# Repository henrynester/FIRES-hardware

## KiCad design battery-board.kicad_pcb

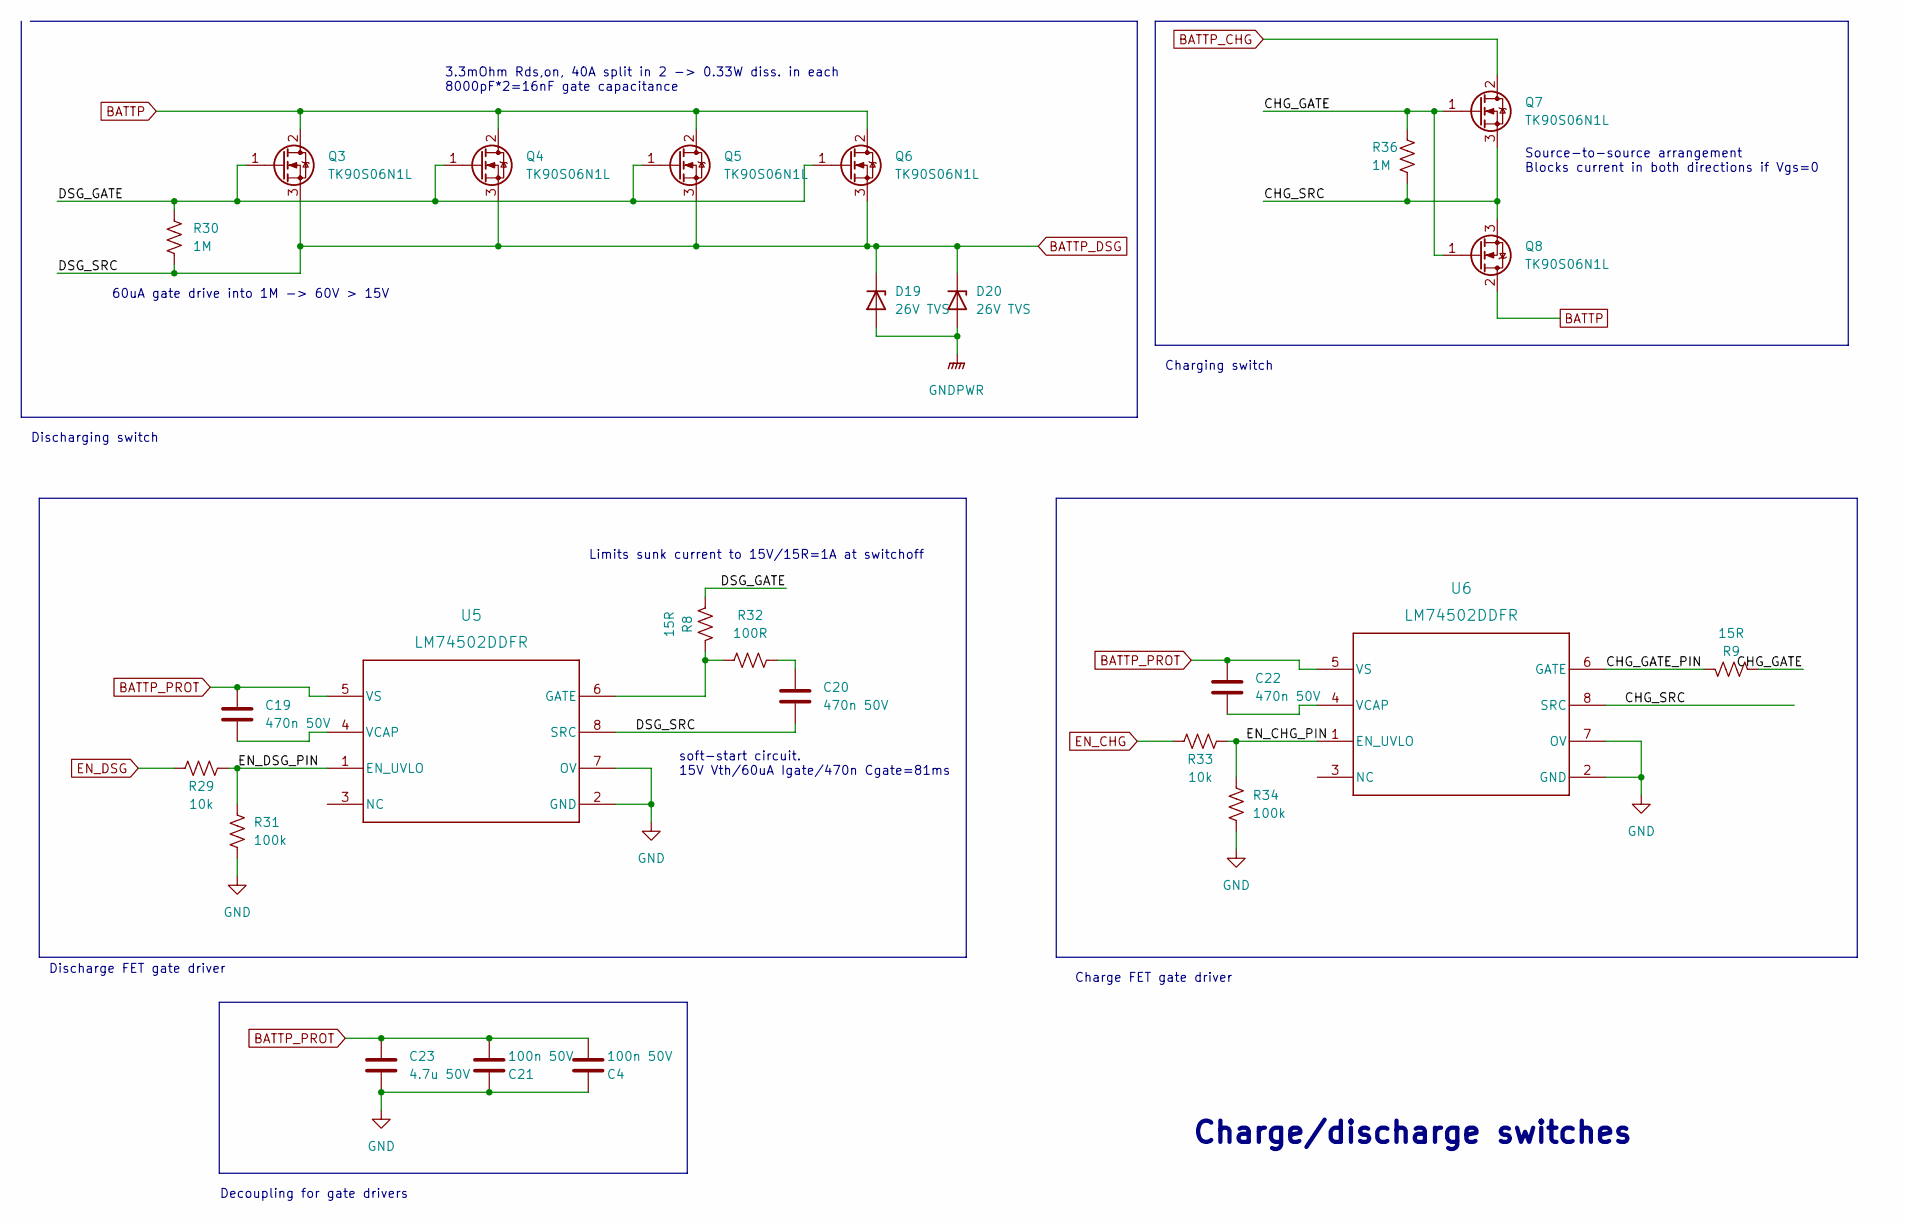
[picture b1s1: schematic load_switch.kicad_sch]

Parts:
C4, C21: 100n 50V; C_0805_2012Metric; part_number GCD21BR71H104KA01L
C19, C20, C22: 470n 50V; C_0805_2012Metric_Pad1.18x1.45mm_HandSolder; part_number GRM21BR71H474KA88L
C23: 4.7u 50V; C_1206_3216Metric_Pad1.33x1.80mm_HandSolder; part_number GRM31CR71H475KA12L
D19, D20: 26V TVS; D_SMB; part_number SMBJ26A
Q3, Q4, Q5, Q6, Q7, Q8: TK90S06N1L; TO-252-2; part_number TK90S06N1L,LXHQ
R8, R9: 15R; R_0805_2012Metric_Pad1.20x1.40mm_HandSolder; part_number RC0805FR-1310KL
R29, R33: 10k; R_0805_2012Metric_Pad1.20x1.40mm_HandSolder; part_number RC0805FR-1310KL
R30, R36: 1M; R_0805_2012Metric_Pad1.20x1.40mm_HandSolder; part_number RC0805FR-071ML
R31, R34: 100k; R_0805_2012Metric_Pad1.20x1.40mm_HandSolder; part_number RC0805FR-07100KL
R32: 100R; R_0805_2012Metric_Pad1.20x1.40mm_HandSolder; part_number RC0805FR-07100RL
U5, U6: LM74502DDFR; LM74502; part_number LM74502DDFR

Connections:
/load_switch/CHG_GATE: Q7.1 (G), Q8.1 (G), R9.2, R36.1
/load_switch/CHG_GATE_PIN: R9.1, U6.6 (GATE)
/load_switch/CHG_SRC: Q7.3 (S), Q8.3 (S), R36.2, U6.8 (SRC)
/load_switch/DSG_GATE: Q3.1 (G), Q4.1 (G), Q5.1 (G), Q6.1 (G), R8.2, R30.1
/load_switch/EN_CHG_PIN: R33.2, R34.1, U6.1 (EN_UVLO)
/load_switch/EN_DSG_PIN: R29.2, R31.1, U5.1 (EN_UVLO)
BATTN: C4.1, C21.1, C23.2, R31.2, R34.2, U5.2 (GND), U5.7 (OV), U6.2 (GND), U6.7 (OV); also elsewhere on the board
BATTP: Q3.2 (D), Q4.2 (D), Q5.2 (D), Q6.2 (D), Q8.2 (D); also elsewhere on the board
BATTP_CHG: Q7.2 (D); also elsewhere on the board
BATTP_DSG: C20.2, D19.1 (K), D20.1 (K), Q3.3 (S), Q4.3 (S), Q5.3 (S), Q6.3 (S), R30.2, U5.8 (SRC); also elsewhere on the board
BATTP_PROT: C4.2, C19.1, C21.2, C22.1, C23.1, U5.5 (VS), U6.5 (VS); also elsewhere on the board
EN_CHG: R33.1; also elsewhere on the board
EN_DSG: R29.1; also elsewhere on the board
GNDPWR: D19.2 (A), D20.2 (A); also elsewhere on the board
unnamed: C19.2, U5.4 (VCAP)
unnamed: C20.1, R32.2
unnamed: C22.2, U6.4 (VCAP)
unnamed: R8.1, R32.1, U5.6 (GATE)

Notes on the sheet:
Charge FET gate driver
Decoupling for gate drivers
soft-start circuit. 15V Vth/60uA Igate/470n Cgate=81ms
Charging switch
Charge/discharge switches
Discharging switch
Discharge FET gate driver
Source-to-source arrangement Blocks current in both directions if Vgs=0
Limits sunk current to 15V/15R=1A at switchoff
60uA gate drive into 1M -> 60V > 15V
3.3mOhm Rds,on, 40A split in 2 -> 0.33W diss. in each 8000pF*2=16nF gate capacitance

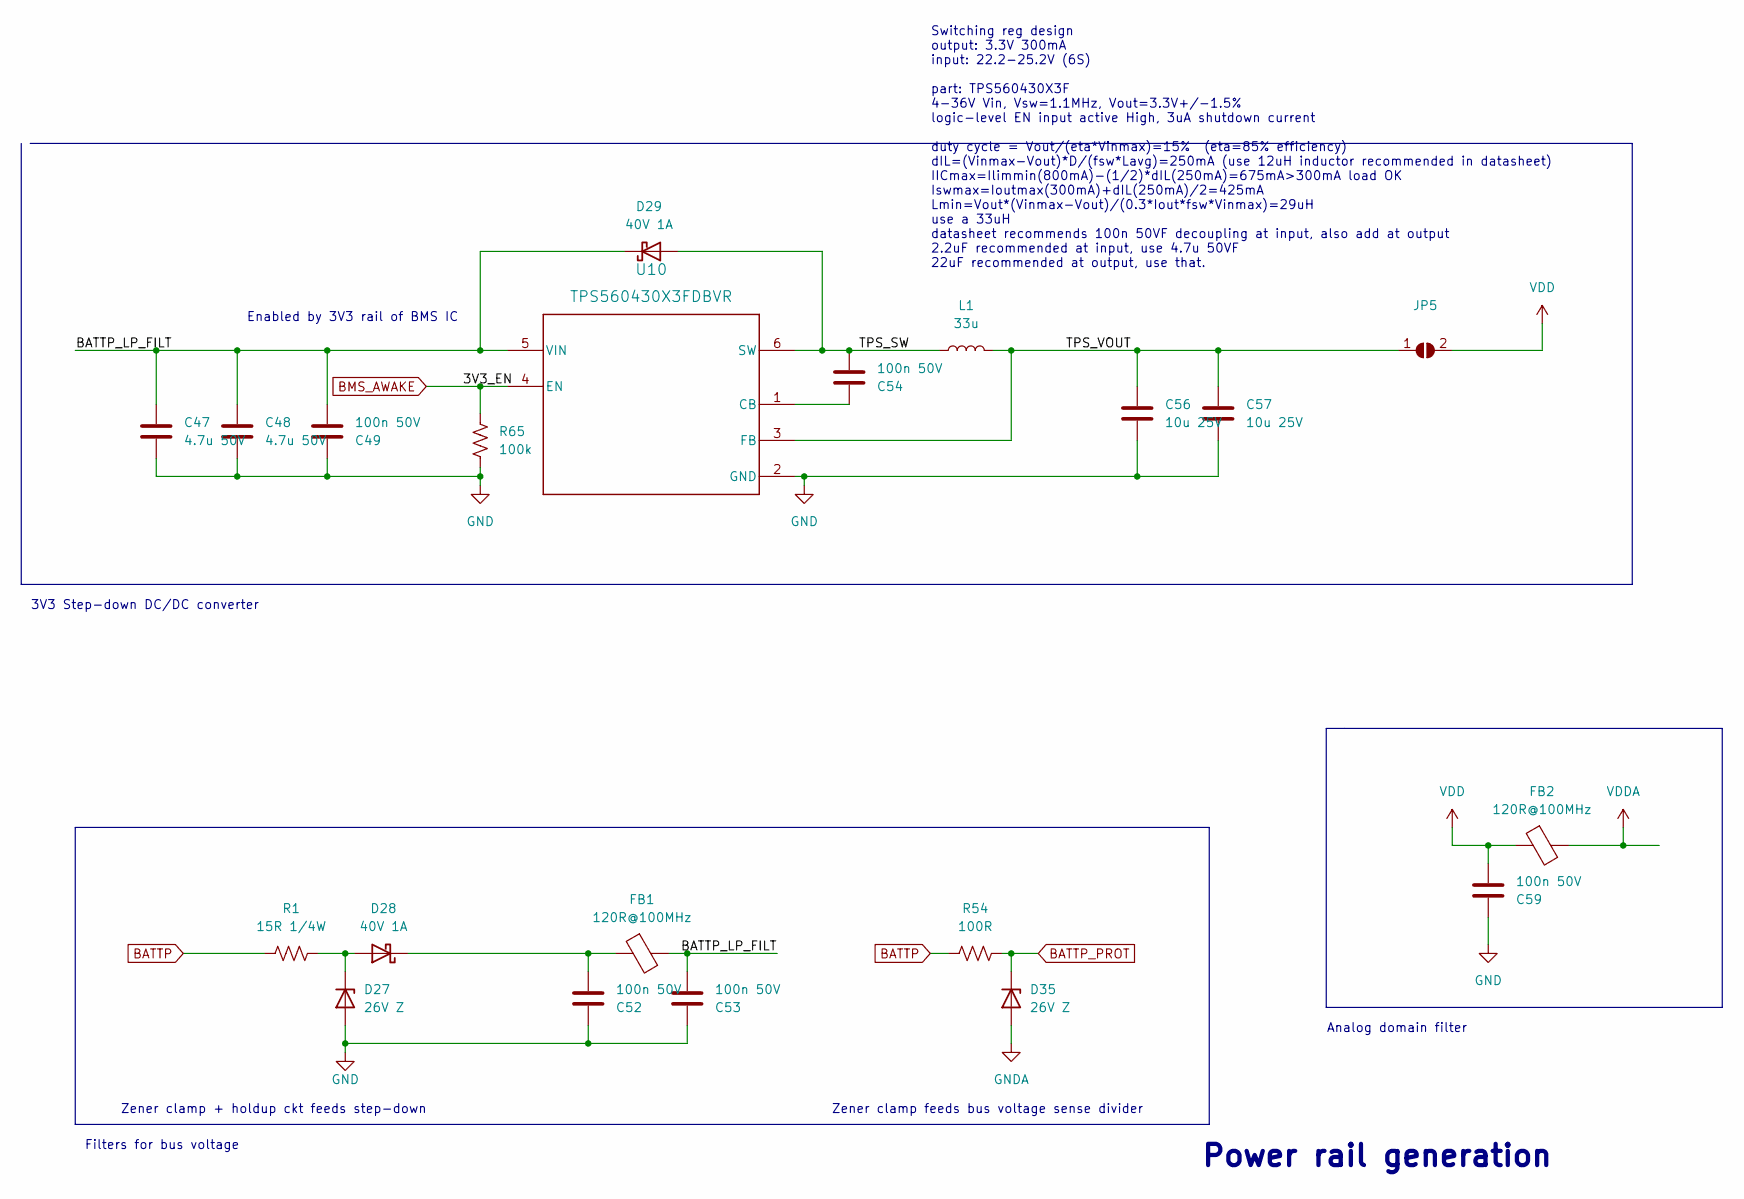
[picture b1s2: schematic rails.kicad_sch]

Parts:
C47, C48: 4.7u 50V; C_1206_3216Metric_Pad1.33x1.80mm_HandSolder; part_number GRM31CR71H475KA12L
C49, C52, C53, C54, C59: 100n 50V; C_0805_2012Metric; part_number GCD21BR71H104KA01L
C56, C57: 10u 25V; C_1206_3216Metric_Pad1.33x1.80mm_HandSolder; part_number GRM31CR71E106KA12L
D27, D35: 26V Z; D_SOD-123; part_number DDZ26-7
D28, D29: 40V 1A; D_SOD-323_HandSoldering; part_number 1N5819WS
FB1, FB2: 120R@100MHz; R_0805_2012Metric; part_number HI0805O121R-10
JP5: SolderJumper-2_P1.3mm_Open_Pad1.0x1.5mm
L1: 33u; L_Taiyo-Yuden_NR-60xx; part_number NR6028T330M
R1: 15R 1/4W; R_0805_2012Metric_Pad1.20x1.40mm_HandSolder; part_number AC0805FR-7W15RL
R54: 100R; R_0805_2012Metric_Pad1.20x1.40mm_HandSolder; part_number RC0805FR-07100RL
R65: 100k; R_0805_2012Metric_Pad1.20x1.40mm_HandSolder; part_number RC0805FR-07100KL
U10: TPS560430X3FDBVR; SOT-23-6_Handsoldering; part_number TPS560430X3FDBVR

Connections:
/rails/BATTP_LP_FILT: C47.1, C48.1, C49.2, C53.2, D29.1 (K), FB1.2, U10.5 (VIN)
/rails/TPS_SW: C54.2, D29.2 (A), L1.1, U10.6 (SW)
/rails/TPS_VOUT: C56.1, C57.1, JP5.1 (A), L1.2, U10.3 (FB)
BATTN: C47.2, C48.2, C49.1, C52.1, C53.1, C56.2, C57.2, C59.1, D27.2 (A), D35.2 (A), R65.1, U10.2 (GND); also elsewhere on the board
BATTP: R1.1, R54.1; also elsewhere on the board
BATTP_PROT: D35.1 (K), R54.2; also elsewhere on the board
BMS_AWAKE: R65.2, U10.4 (EN); also elsewhere on the board
unnamed: C52.2, D28.1 (K), FB1.1
unnamed: C54.1, U10.1 (CB)
unnamed: D27.1 (K), D28.2 (A), R1.2
VDD: C59.2, FB2.1, JP5.2 (B); also elsewhere on the board
VDDA: FB2.2; also elsewhere on the board

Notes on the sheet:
3V3 Step-down DC/DC converter
Analog domain filter
Zener clamp feeds bus voltage sense divider
Power rail generation
Switching reg design output: 3.3V 300mA input: 22.2-25.2V (6S) part: TPS560430X3F 4-36V Vin, Vsw=1.1MHz, Vout=3.3V+/-1.5% logic-level EN input active High, 3uA shutdown current duty cycle = Vout/(eta*Vinmax)=15% (eta=85% efficiency) dIL=(Vinmax-Vout)*D/(fsw*Lavg)=250mA (use 12uH inductor recommende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
Filters for bus voltage
Zener clamp + holdup ckt feeds step-down
Enabled by 3V3 rail of BMS IC

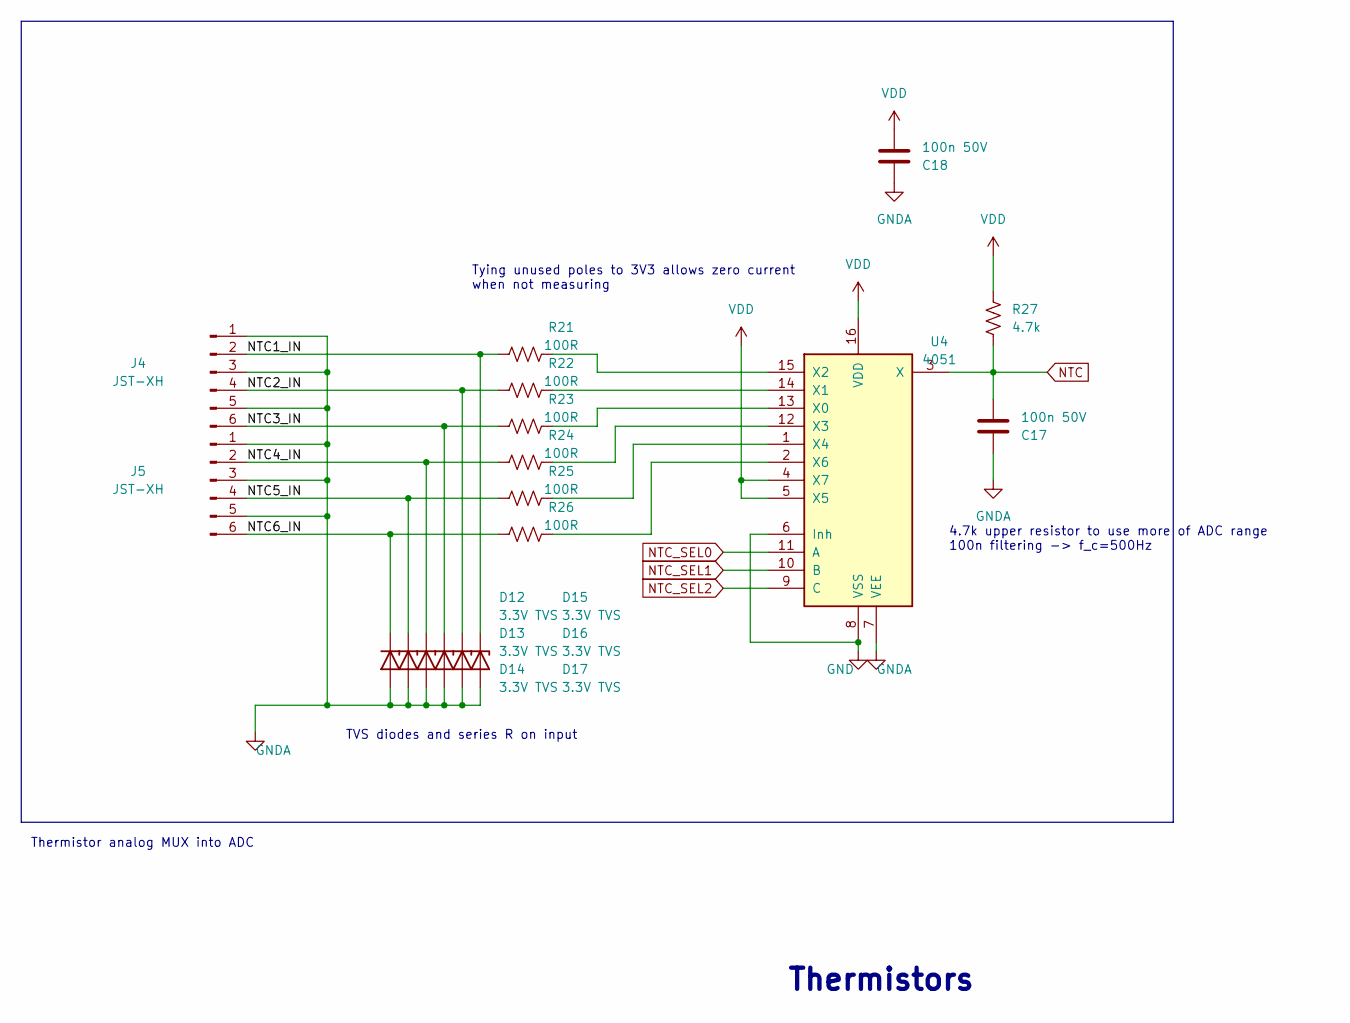
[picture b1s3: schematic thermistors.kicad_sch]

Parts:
C17, C18: 100n 50V; C_0805_2012Metric; part_number GCD21BR71H104KA01L
D12, D13, D14, D15, D16, D17: 3.3V TVS; D_SOD-323_HandSoldering; part_number ESD5Z3.3T5G
J4, J5: JST-XH; JST_XH_B6B-XH-A_1x06_P2.50mm_Vertical
R21, R22, R23, R24, R25, R26: 100R; R_0805_2012Metric_Pad1.20x1.40mm_HandSolder; part_number RC0805FR-07100RL
R27: 4.7k; R_0805_2012Metric_Pad1.20x1.40mm_HandSolder; part_number RC0805FR-074K7L
U4: 4051; TSSOP-16_4.4x5mm_P0.65mm; part_number CD74HC4051PWR

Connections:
/thermistors/NTC1_IN: D17.1 (K), J4.2, R21.2
/thermistors/NTC2_IN: D16.1 (K), J4.4, R22.2
/thermistors/NTC3_IN: D15.1 (K), J4.6, R23.2
/thermistors/NTC4_IN: D14.1 (K), J5.2, R24.2
/thermistors/NTC5_IN: D13.1 (K), J5.4, R25.2
/thermistors/NTC6_IN: D12.1 (K), J5.6, R26.2
BATTN: C17.1, C18.1, D12.2 (A), D13.2 (A), D14.2 (A), D15.2 (A), D16.2 (A), D17.2 (A), J4.1, J4.3, J4.5, J5.1, J5.3, J5.5, U4.6 (Inh), U4.7 (VEE), U4.8 (VSS); also elsewhere on the board
NTC: C17.2, R27.2, U4.3 (X); also elsewhere on the board
NTC_SEL0: U4.11 (A); also elsewhere on the board
NTC_SEL1: U4.10 (B); also elsewhere on the board
NTC_SEL2: U4.9 (C); also elsewhere on the board
unnamed: R21.1, U4.15 (X2)
unnamed: R22.1, U4.14 (X1)
unnamed: R23.1, U4.13 (X0)
unnamed: R24.1, U4.12 (X3)
unnamed: R25.1, U4.1 (X4)
unnamed: R26.1, U4.2 (X6)
VDD: C18.2, R27.1, U4.4 (X7), U4.5 (X5), U4.16 (VDD); also elsewhere on the board

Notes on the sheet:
TVS diodes and series R on input
4.7k upper resistor to use more of ADC range 100n filtering -> f_c=500Hz
Tying unused poles to 3V3 allows zero current when not measuring
Thermistors
Thermistor analog MUX into ADC

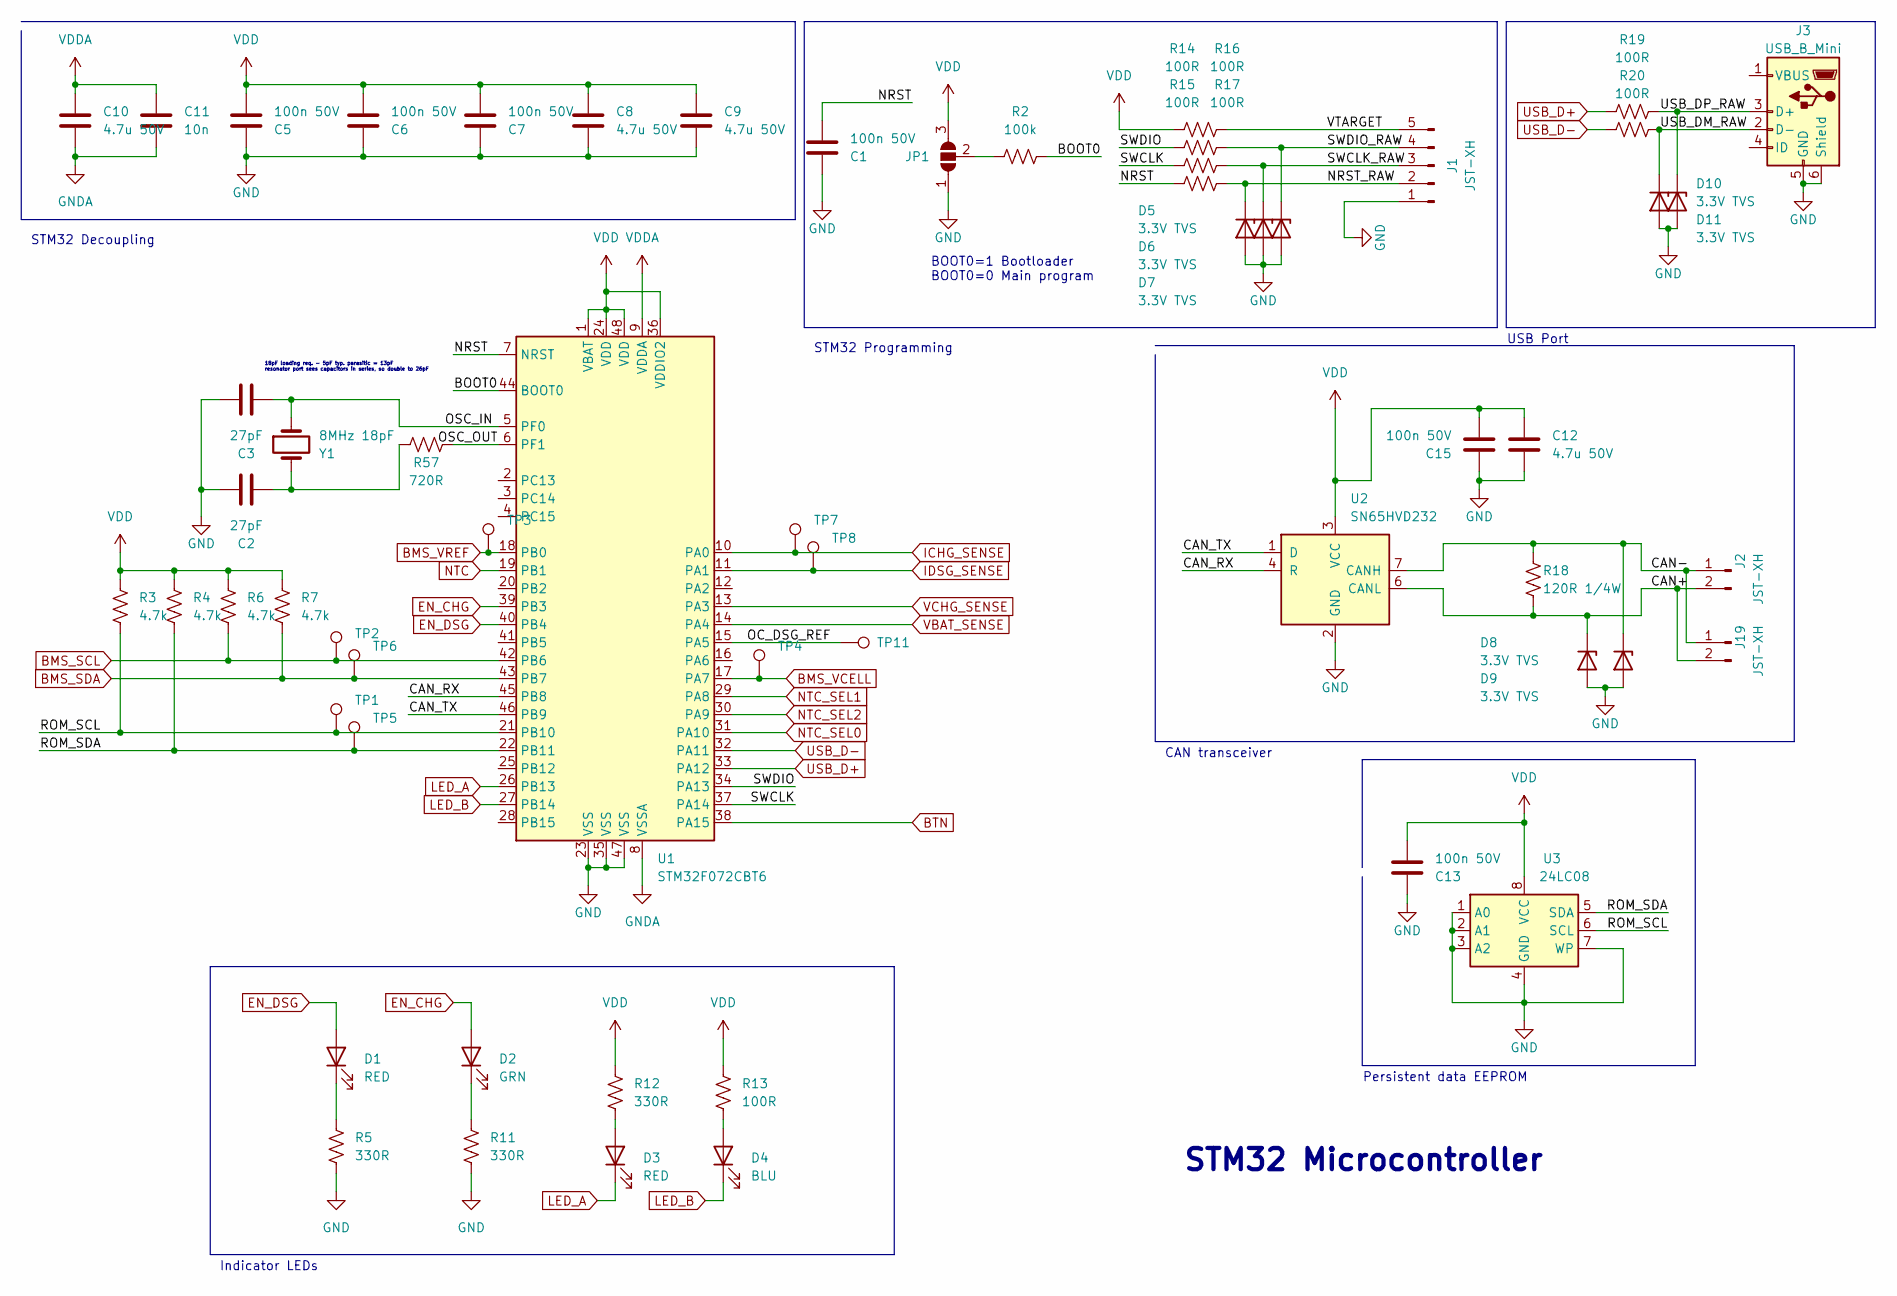
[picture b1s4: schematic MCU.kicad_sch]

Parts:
C1, C5, C6, C7, C13, C15: 100n 50V; C_0805_2012Metric; part_number GCD21BR71H104KA01L
C2, C3: 27pF; C_0805_2012Metric_Pad1.18x1.45mm_HandSolder; part_number CC0805FRNPO9BN270
C8, C9, C10, C12: 4.7u 50V; C_1206_3216Metric_Pad1.33x1.80mm_HandSolder; part_number GRM31CR71H475KA12L
C11: 10n; R_0805_2012Metric_Pad1.20x1.40mm_HandSolder; part_number GCM219R71H103KA37D
D1, D3: RED; LED_0805_2012Metric_Pad1.15x1.40mm_HandSolder; part_number LTST-C171KRKT
D2: GRN; LED_0805_2012Metric_Pad1.15x1.40mm_HandSolder; part_number LTST-C171GKT
D4: BLU; LED_0805_2012Metric_Pad1.15x1.40mm_HandSolder; part_number LTST-C171TBKT
D5, D6, D7, D8, D9, D10, D11: 3.3V TVS; D_SOD-323_HandSoldering; part_number ESD5Z3.3T5G
J1: JST-XH; PinHeader_1x05_P2.54mm_Vertical
J2, J19: JST-XH; JST_XH_B2B-XH-A_1x02_P2.50mm_Vertical
J3: USB_B_Mini; USB_Mini-B_Tensility_54-00023_Vertical; part_number 54-00023
JP1: SolderJumper-3_P1.3mm_Open_Pad1.0x1.5mm
R2: 100k; R_0805_2012Metric_Pad1.20x1.40mm_HandSolder; part_number RC0805FR-07100KL
R3, R4, R6, R7: 4.7k; R_0805_2012Metric_Pad1.20x1.40mm_HandSolder; part_number RC0805FR-074K7L
R5, R11, R12: 330R; R_0805_2012Metric_Pad1.20x1.40mm_HandSolder; part_number RC0805FR-07100RL
R13, R14, R15, R16, R17, R19, R20: 100R; R_0805_2012Metric_Pad1.20x1.40mm_HandSolder; part_number RC0805FR-07100RL
R18: 120R 1/4W; R_0805_2012Metric_Pad1.20x1.40mm_HandSolder; part_number RC0805FR-7W120RL
R57: 720R; R_0805_2012Metric_Pad1.20x1.40mm_HandSolder; part_number RC0805FR-07100RL
TP1, TP2, TP3, TP4, TP5, TP6, TP7, TP8: PinHeader_1x01_P1.00mm_Vertical
TP11: TestPoint; TestPoint_Pad_D1.0mm
U1: STM32F072CBT6; LQFP-48_7x7mm_P0.5mm; part_number STM32F072CBT6
U2: SN65HVD232; SOIC-8_3.9x4.9mm_P1.27mm; part_number SN65HVD232
U3: 24LC08; SOIC-8_3.9x4.9mm_P1.27mm; part_number 24LC08BT-I/SN
Y1: 8MHz 18pF; Crystal_SMD_HC49-SD; part_number ABLS-8.000MHZ-D-T

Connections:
/MCU/BOOT0: R2.2, U1.44 (BOOT0)
/MCU/CAN+: D8.1 (K), J2.2, J19.2, R18.2, U2.6 (CANL)
/MCU/CAN-: D9.1 (K), J2.1, J19.1, R18.1, U2.7 (CANH)
/MCU/CAN_RX: U1.45 (PB8), U2.4 (R)
/MCU/CAN_TX: U1.46 (PB9), U2.1 (D)
/MCU/NRST: C1.2, R17.2, U1.7 (NRST)
/MCU/NRST_RAW: D5.1 (K), J1.2, R17.1
/MCU/OC_DSG_REF: TP11.1, U1.15 (PA5)
/MCU/OSC_IN: C3.2, U1.5 (PF0), Y1.1
/MCU/OSC_OUT: R57.2, U1.6 (PF1)
/MCU/ROM_SCL: R3.2, TP1.1, U1.21 (PB10), U3.6 (SCL)
/MCU/ROM_SDA: R4.2, TP5.1, U1.22 (PB11), U3.5 (SDA)
/MCU/SWCLK: R16.2, U1.37 (PA14)
/MCU/SWCLK_RAW: D6.1 (K), J1.3, R16.1
/MCU/SWDIO: R15.2, U1.34 (PA13)
/MCU/SWDIO_RAW: D7.1 (K), J1.4, R15.1
/MCU/USB_DM_RAW: D10.1 (K), J3.2 (D-), R20.1
/MCU/USB_DP_RAW: D11.1 (K), J3.3 (D+), R19.1
/MCU/VTARGET: J1.5, R14.1
BATTN: C1.1, C2.1, C3.1, C5.1, C6.1, C7.1, C8.2, C9.2, C10.2, C11.2, C12.2, C13.1, C15.1, D5.2 (A), D6.2 (A), D7.2 (A), D8.2 (A), D9.2 (A), D10.2 (A), D11.2 (A), J1.1, J3.5 (GND), J3.6 (Shield), JP1.1 (A), R5.1, R11.1, U1.8 (VSSA), U1.23 (VSS), U1.35 (VSS), U1.47 (VSS), U2.2 (GND), U3.1 (A0), U3.2 (A1), U3.3 (A2), U3.4 (GND), U3.7 (WP); also elsewhere on the board
BMS_SCL: R6.2, TP2.1, U1.42 (PB6); also elsewhere on the board
BMS_SDA: R7.2, TP6.1, U1.43 (PB7); also elsewhere on the board
BMS_VCELL: TP4.1, U1.17 (PA7); also elsewhere on the board
BMS_VREF: TP3.1, U1.18 (PB0); also elsewhere on the board
BTN: U1.38 (PA15); also elsewhere on the board
EN_CHG: D2.2 (A), U1.39 (PB3); also elsewhere on the board
EN_DSG: D1.2 (A), U1.40 (PB4); also elsewhere on the board
ICHG_SENSE: TP7.1, U1.10 (PA0); also elsewhere on the board
IDSG_SENSE: TP8.1, U1.11 (PA1); also elsewhere on the board
LED_A: D3.1 (K), U1.26 (PB13)
LED_B: D4.1 (K), U1.27 (PB14)
NTC: U1.19 (PB1); also elsewhere on the board
NTC_SEL0: U1.31 (PA10); also elsewhere on the board
NTC_SEL1: U1.29 (PA8); also elsewhere on the board
NTC_SEL2: U1.30 (PA9); also elsewhere on the board
unnamed: C2.2, R57.1, Y1.2
unnamed: D1.1 (K), R5.2
unnamed: D2.1 (K), R11.2
unnamed: D3.2 (A), R12.1
unnamed: D4.2 (A), R13.1
unnamed: JP1.2 (C), R2.1
USB_D+: R19.2, U1.33 (PA12)
USB_D-: R20.2, U1.32 (PA11)
VBAT_SENSE: U1.14 (PA4); also elsewhere on the board
VCHG_SENSE: U1.13 (PA3); also elsewhere on the board
VDD: C5.2, C6.2, C7.2, C8.1, C9.1, C12.1, C13.2, C15.2, JP1.3 (B), R3.1, R4.1, R6.1, R7.1, R12.2, R13.2, R14.2, U1.1 (VBAT), U1.24 (VDD), U1.36 (VDDIO2), U1.48 (VDD), U2.3 (VCC), U3.8 (VCC); also elsewhere on the board
VDDA: C10.1, C11.1, U1.9 (VDDA); also elsewhere on the board

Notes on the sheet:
Persistent data EEPROM
USB Port
18pF loading req. - 5pF typ. parasitic = 13pF resonator port sees capacitors in series, so double to 26pF
BOOT0=1 Bootloader BOOT0=0 Main program
STM32 Programming
Indicator LEDs
CAN transceiver
STM32 Decoupling
STM32 Microcontroller

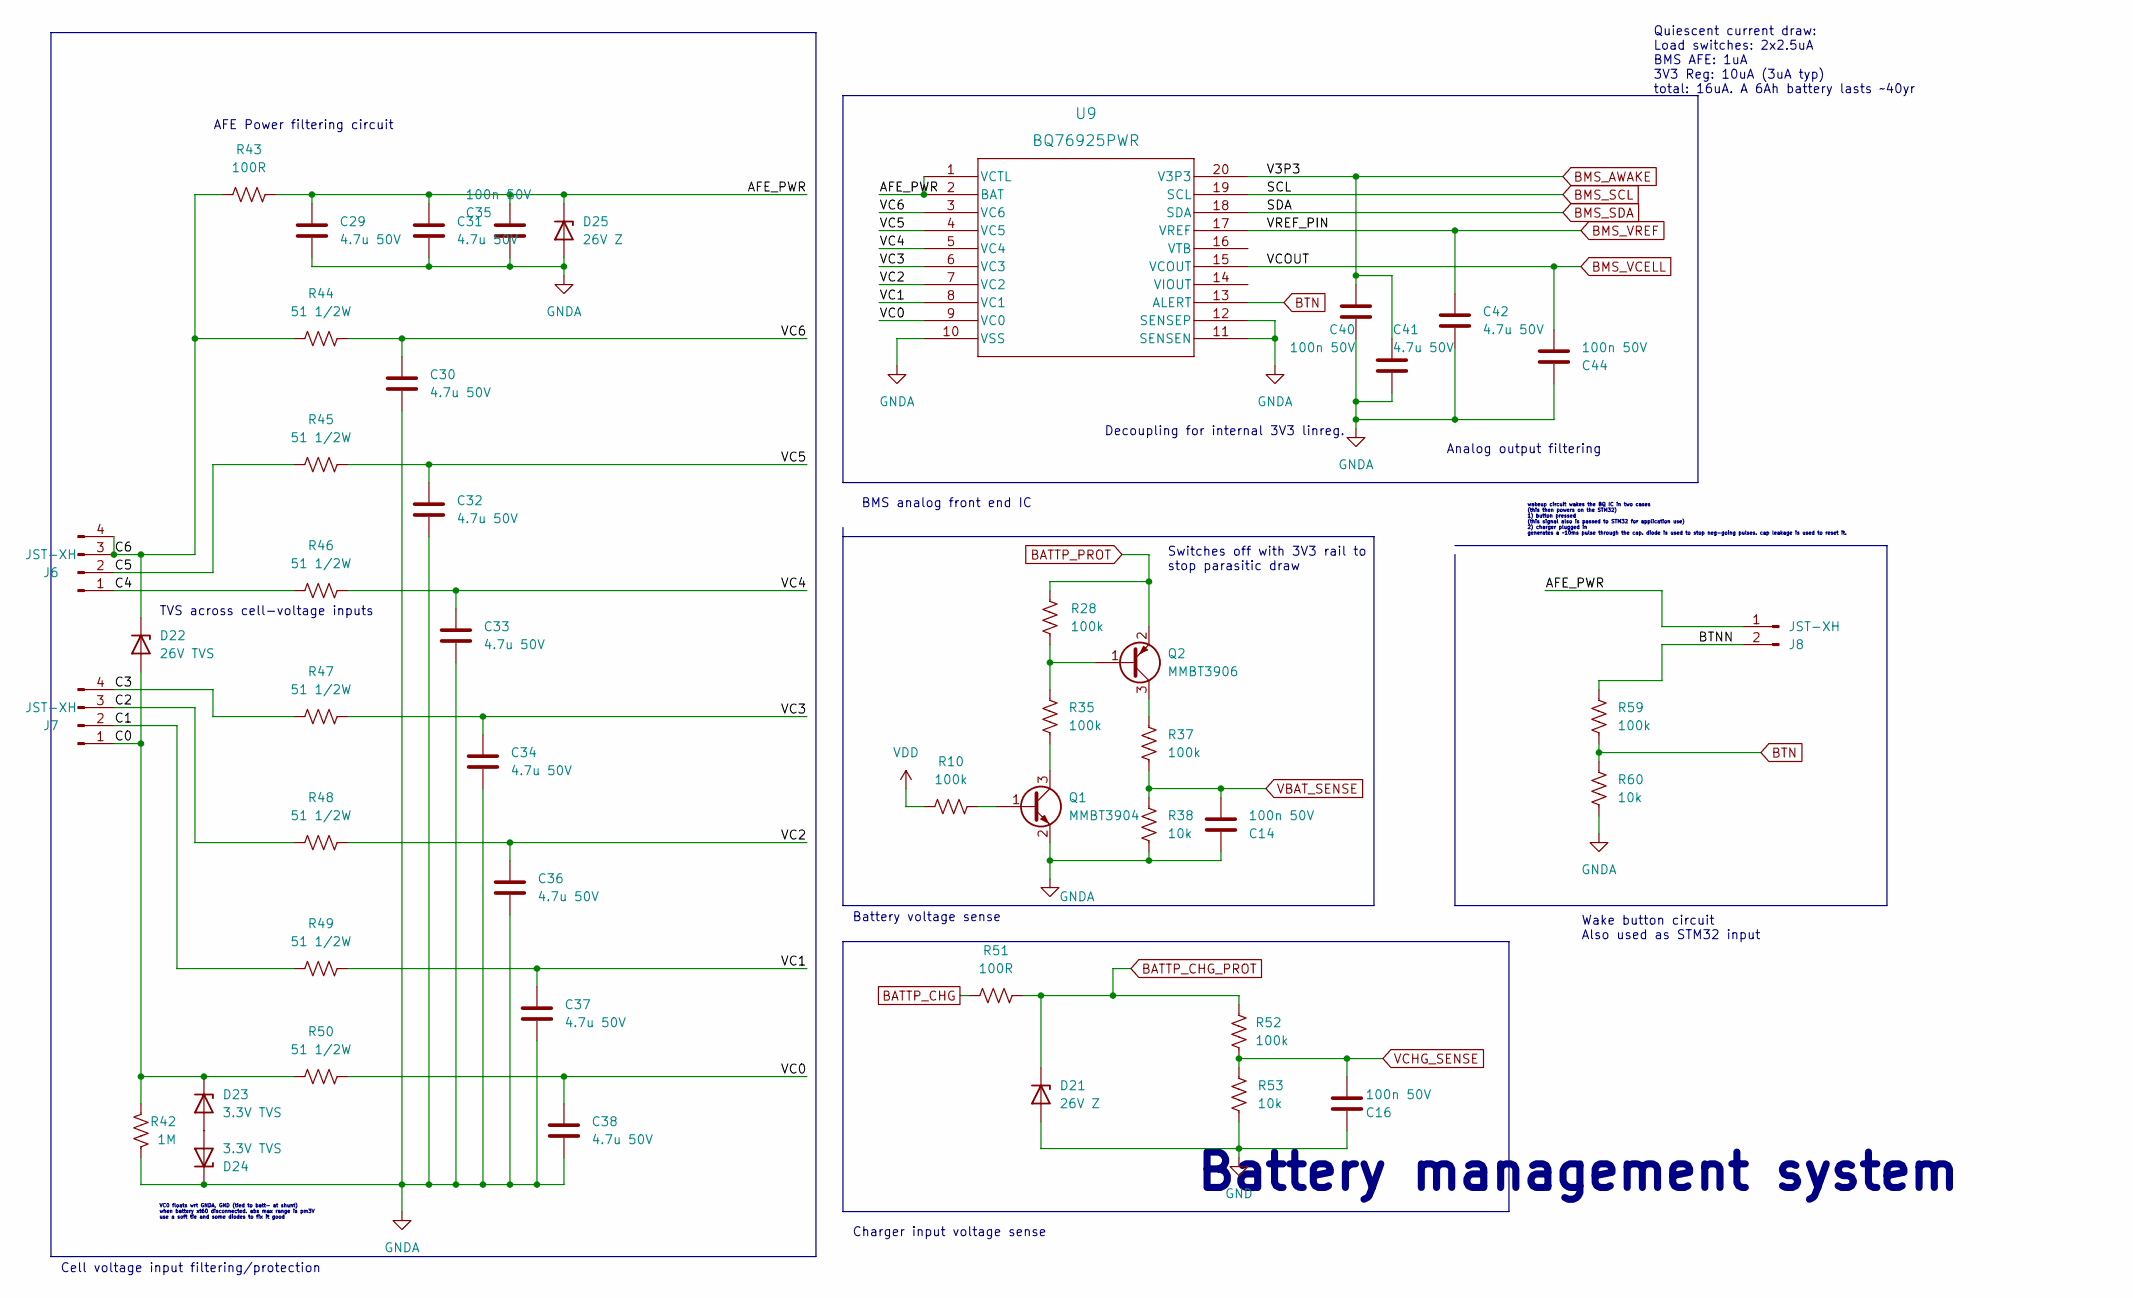
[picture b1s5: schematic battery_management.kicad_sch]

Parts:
C14, C16, C35, C40, C44: 100n 50V; C_0805_2012Metric; part_number GCD21BR71H104KA01L
C29, C30, C31, C32, C33, C34, C36, C37, C38, C41, C42: 4.7u 50V; C_1206_3216Metric_Pad1.33x1.80mm_HandSolder; part_number GRM31CR71H475KA12L
D21, D25: 26V Z; D_SOD-123; part_number DDZ26-7
D22: 26V TVS; D_SMB_Handsoldering; part_number SMBJ26A
D23, D24: 3.3V TVS; D_SOD-323_HandSoldering; part_number ESD5Z3.3T5G
J6, J7: JST-XH; JST_XH_B4B-XH-A_1x04_P2.50mm_Vertical
J8: JST-XH; JST_XH_B2B-XH-A_1x02_P2.50mm_Vertical
Q1: MMBT3904; SOT-23; part_number MMBT3904
Q2: MMBT3906; SOT-23; part_number MMBT3906
R10, R28, R35, R37, R52, R59: 100k; R_0805_2012Metric_Pad1.20x1.40mm_HandSolder; part_number RC0805FR-07100KL
R38, R53, R60: 10k; R_0805_2012Metric_Pad1.20x1.40mm_HandSolder; part_number RC0805FR-1310KL
R42: 1M; R_0805_2012Metric_Pad1.20x1.40mm_HandSolder; part_number RC0805FR-071ML
R43, R51: 100R; R_0805_2012Metric_Pad1.20x1.40mm_HandSolder; part_number RC0805FR-07100RL
R44, R45, R46, R47, R48, R49, R50: 51 1/2W; R_1206_3216Metric_Pad1.30x1.75mm_HandSolder; part_number CRM1206-FX-51R0ELF
U9: BQ76925PWR; BQ76925; part_number BQ76925PWR

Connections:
/battery_management/AFE_PWR: C29.1, C31.1, C35.2, D25.1 (K), J8.1, R43.2, U9.1 (VCTL), U9.2 (BAT)
/battery_management/BTNN: J8.2, R59.1
/battery_management/C0: D22.2 (A), D23.1 (K), J7.1, R42.1, R50.2
/battery_management/C1: J7.2, R49.2
/battery_management/C2: J7.3, R48.2
/battery_management/C3: J7.4, R47.2
/battery_management/C4: J6.1, R46.2
/battery_management/C5: J6.2, R45.2
/battery_management/C6: D22.1 (K), J6.3, J6.4, R43.1, R44.2
/battery_management/VC0: C38.1, R50.1, U9.9 (VC0)
/battery_management/VC1: C37.1, R49.1, U9.8 (VC1)
/battery_management/VC2: C36.1, R48.1, U9.7 (VC2)
/battery_management/VC3: C34.1, R47.1, U9.6 (VC3)
/battery_management/VC4: C33.1, R46.1, U9.5 (VC4)
/battery_management/VC5: C32.1, R45.1, U9.4 (VC5)
/battery_management/VC6: C30.1, R44.1, U9.3 (VC6)
BATTN: C14.1, C16.1, C29.2, C30.2, C31.2, C32.2, C33.2, C34.2, C35.1, C36.2, C37.2, C38.2, C40.1, C41.2, C42.2, C44.1, D21.2 (A), D24.1 (K), D25.2 (A), Q1.2 (E), R38.2, R42.2, R53.2, R60.2, U9.10 (VSS), U9.11 (SENSEN), U9.12 (SENSEP); also elsewhere on the board
BATTP_CHG: R51.1; also elsewhere on the board
BATTP_CHG_PROT: D21.1 (K), R51.2, R52.1
BATTP_PROT: Q2.2 (E), R28.2; also elsewhere on the board
BMS_AWAKE: C40.2, C41.1, U9.20 (V3P3); also elsewhere on the board
BMS_SCL: U9.19 (SCL); also elsewhere on the board
BMS_SDA: U9.18 (SDA); also elsewhere on the board
BMS_VCELL: C44.2, U9.15 (VCOUT); also elsewhere on the board
BMS_VREF: C42.1, U9.17 (VREF); also elsewhere on the board
BTN: R59.2, R60.1, U9.13 (ALERT); also elsewhere on the board
unnamed: D23.2 (A), D24.2 (A)
unnamed: Q1.1 (B), R10.2
unnamed: Q1.3 (C), R35.1
unnamed: Q2.1 (B), R28.1, R35.2
unnamed: Q2.3 (C), R37.2
VBAT_SENSE: C14.2, R37.1, R38.1; also elsewhere on the board
VCHG_SENSE: C16.2, R52.2, R53.1; also elsewhere on the board
VDD: R10.1; also elsewhere on the board

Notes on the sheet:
Battery voltage sense
Decoupling for internal 3V3 linreg.
Wake button circuit Also used as STM32 input
Cell voltage input filtering/protection
Switches off with 3V3 rail to stop parasitic draw
AFE Power filtering circuit
VC0 floats wrt GNDA, GND (tied to batt- at shunt) when battery xt60 disconnected. abs max range is pm3V use a soft tie and some diodes to fix it good
Quiescent current draw: Load switches: 2x2.5uA BMS AFE: 1uA 3V3 Reg: 10uA (3uA typ) total: 16uA. A 6Ah battery lasts ~40yr
TVS across cell-voltage inputs
Battery management system
Analog output filtering
BMS analog front end IC
Charger input voltage sense
wakeup circuit wakes the BQ IC in two cases (this then powers on the STM32) 1) button pressed (this signal also is passed to STM32 for application use) 2) charger plugged in generates a ~10ms pulse through the cap. diode is used to stop neg-going pulses. cap leakage is used to reset it.

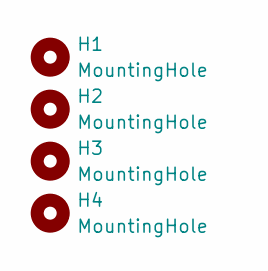
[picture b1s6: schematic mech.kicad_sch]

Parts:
H1, H2, H3, H4: MountingHole; MountingHole_3.2mm_M3

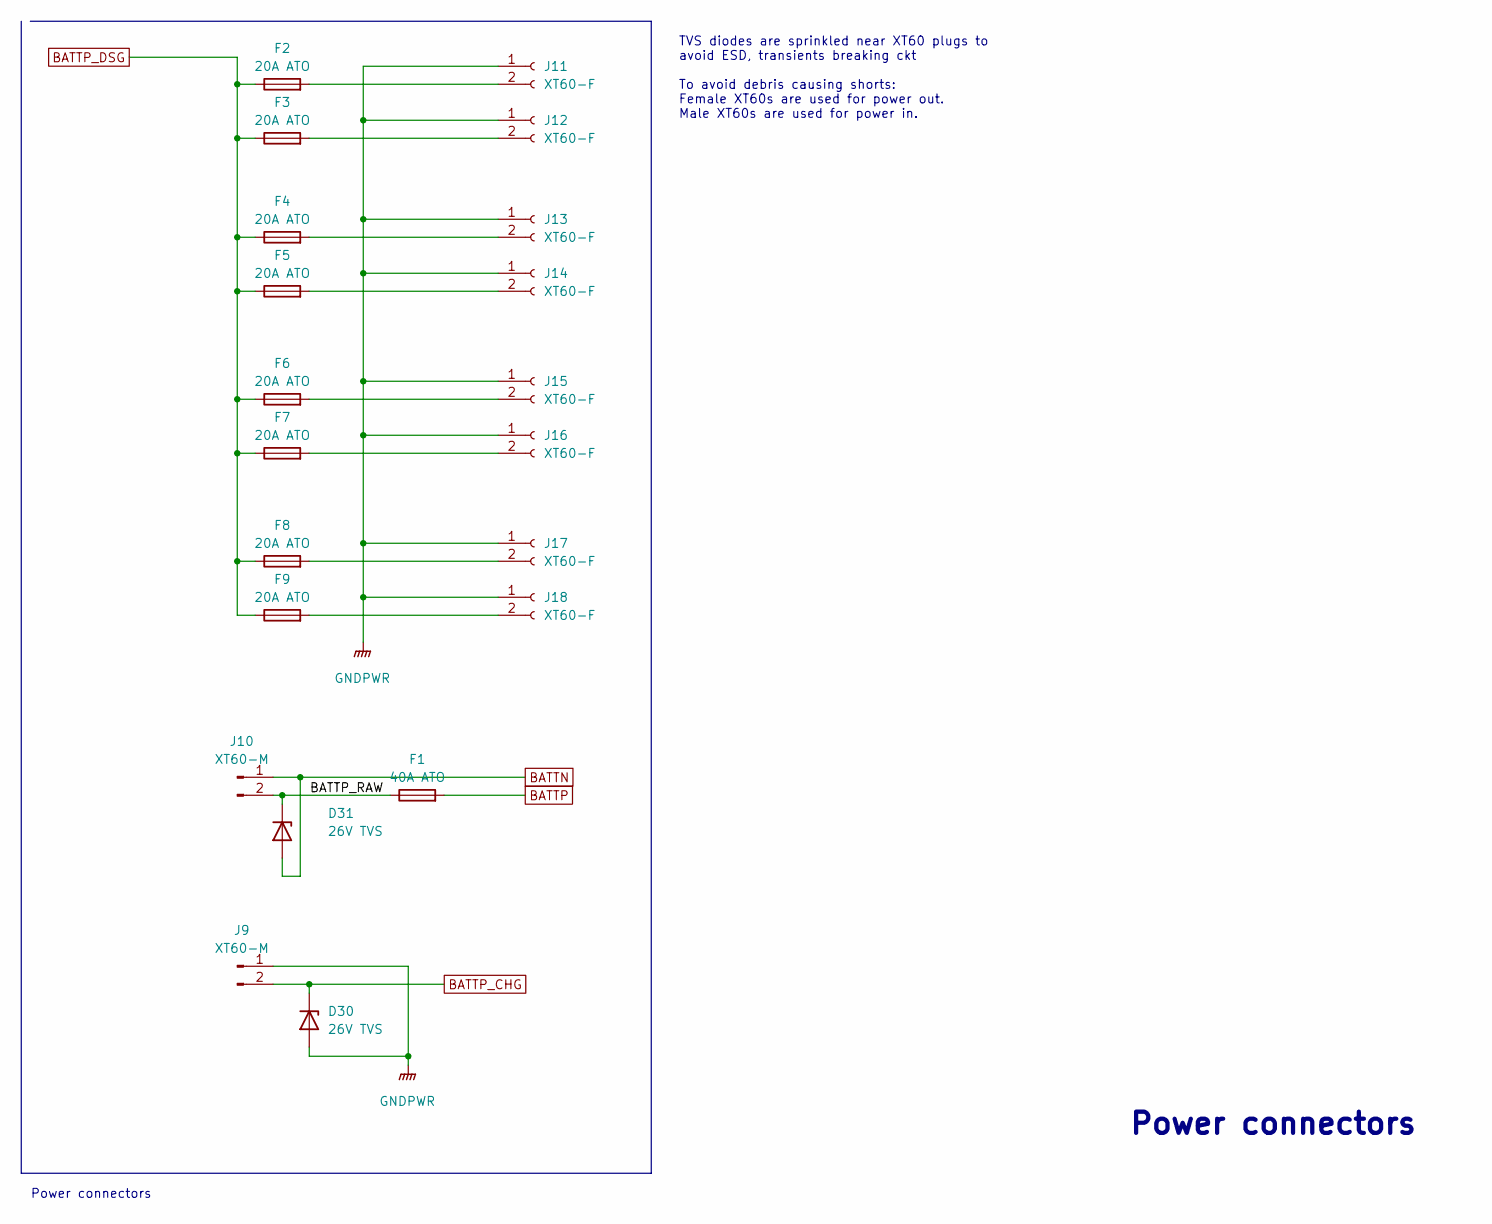
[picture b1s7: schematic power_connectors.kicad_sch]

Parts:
D30, D31: 26V TVS; D_SMB; part_number SMBJ26A
F1: 40A ATO; 3522-2; part_number 3522-2
F2, F3, F4, F5, F6, F7, F8, F9: 20A ATO; 3522-2; part_number 3522-2
J9, J10: XT60-M; AMASS_XT60-M_1x02_P7.20mm_Vertical
J11, J12, J13, J14, J15, J16, J17, J18: XT60-F; AMASS_XT60-F_1x02_P7.20mm_Vertical

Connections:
/power_connectors/BATTP_RAW: D31.1 (K), F1.1, J10.2
BATTN: D31.2 (A), J10.1; also elsewhere on the board
BATTP: F1.2; also elsewhere on the board
BATTP_CHG: D30.1 (K), J9.2; also elsewhere on the board
BATTP_DSG: F2.1, F3.1, F4.1, F5.1, F6.1, F7.1, F8.1, F9.1; also elsewhere on the board
GNDPWR: D30.2 (A), J9.1, J11.1, J12.1, J13.1, J14.1, J15.1, J16.1, J17.1, J18.1; also elsewhere on the board
unnamed: F2.2, J11.2
unnamed: F3.2, J12.2
unnamed: F4.2, J13.2
unnamed: F5.2, J14.2
unnamed: F6.2, J15.2
unnamed: F7.2, J16.2
unnamed: F8.2, J17.2
unnamed: F9.2, J18.2

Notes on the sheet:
TVS diodes are sprinkled near XT60 plugs to avoid ESD, transients breaking ckt To avoid debris causing shorts: Female XT60s are used for power out. Male XT60s are used for power in.
Power connectors
